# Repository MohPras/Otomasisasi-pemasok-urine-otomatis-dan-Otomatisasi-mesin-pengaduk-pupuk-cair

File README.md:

# Otomasisasi-pemasok-urine-otomatis-dan-Otomatisasi-mesin-pengaduk-pupuk-cair

Alat ini berfungsi untuk membuat pupuk secara otomatis dimana letak otomasisasinya itu pada saat memasukan urine domba dan saat proses pengadukan. Cara kerja alat ini pertama saat pushbutton urine ditekan makan dia akan mengeluarkan urine sebanyak yang kita mau, untuk perhitunganya menggunakan flow sensor sedangkan kran otomatis menggunakan valve sehingga kita bisa dengan mudah mengatur kapasitas urine yang akan dimasukan. Setelah kaspitas air sudah sesuai dengan yang dimau kran akan tertutup otomatis. dan selanjutnya relay akan mengaktifkan motor pengaduknya selama 20 menit dan pupuk pun jadi.

Alat dan bahan
- motor + gir box
- flow sensor
- valve
- sensor proximity untuk mengetahui berapa banyak urine dalam tampungan
- relay sebagai saklar otomatis

Design PCB

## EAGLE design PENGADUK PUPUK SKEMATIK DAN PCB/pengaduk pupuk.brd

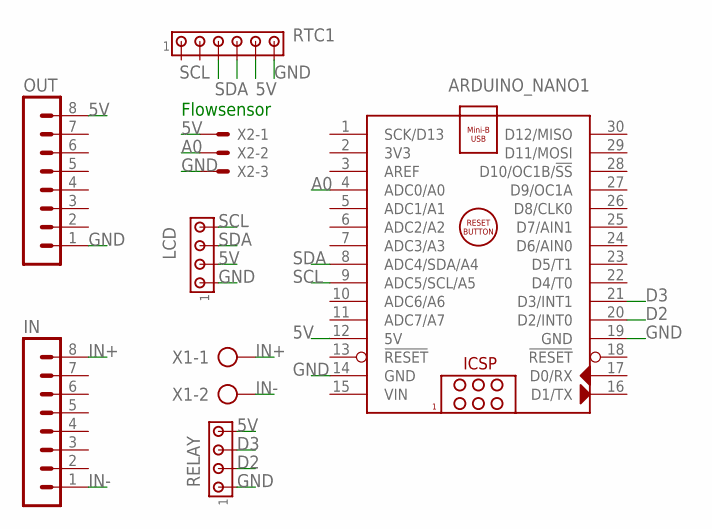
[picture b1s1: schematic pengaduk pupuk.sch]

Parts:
ARDUINO_NANO1: ARDUINO_NANO
IN: MA08-1
LCD: MTA04-100; 10X04MTA
OUT: MA08-1
RELAY: MTA04-100; 10X04MTA
RTC1: MTA06-100; 10X06MTA
X1: AK500/2-H
X2: KK-156-3

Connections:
5V: ARDUINO_NANO1.12 (5V), LCD.2, OUT.8, RELAY.4, RTC1.5, X2.1
A0: ARDUINO_NANO1.4 (ADC0/A0), X2.2
D2: ARDUINO_NANO1.20 (D2/INT0), RELAY.2
D3: ARDUINO_NANO1.21 (D3/INT1), RELAY.3
GND: ARDUINO_NANO1.14 (GND), ARDUINO_NANO1.19 (GND), LCD.1, OUT.1, RELAY.1, RTC1.6, X2.3
IN+: IN.8, X1.1
IN-: IN.1, X1.2
SCL: ARDUINO_NANO1.9 (ADC5/SCL/A5), LCD.4, RTC1.3
SDA: ARDUINO_NANO1.8 (ADC4/SDA/A4), LCD.3, RTC1.4
VIN: ARDUINO_NANO1.15 (VIN)

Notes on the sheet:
Flowsensor

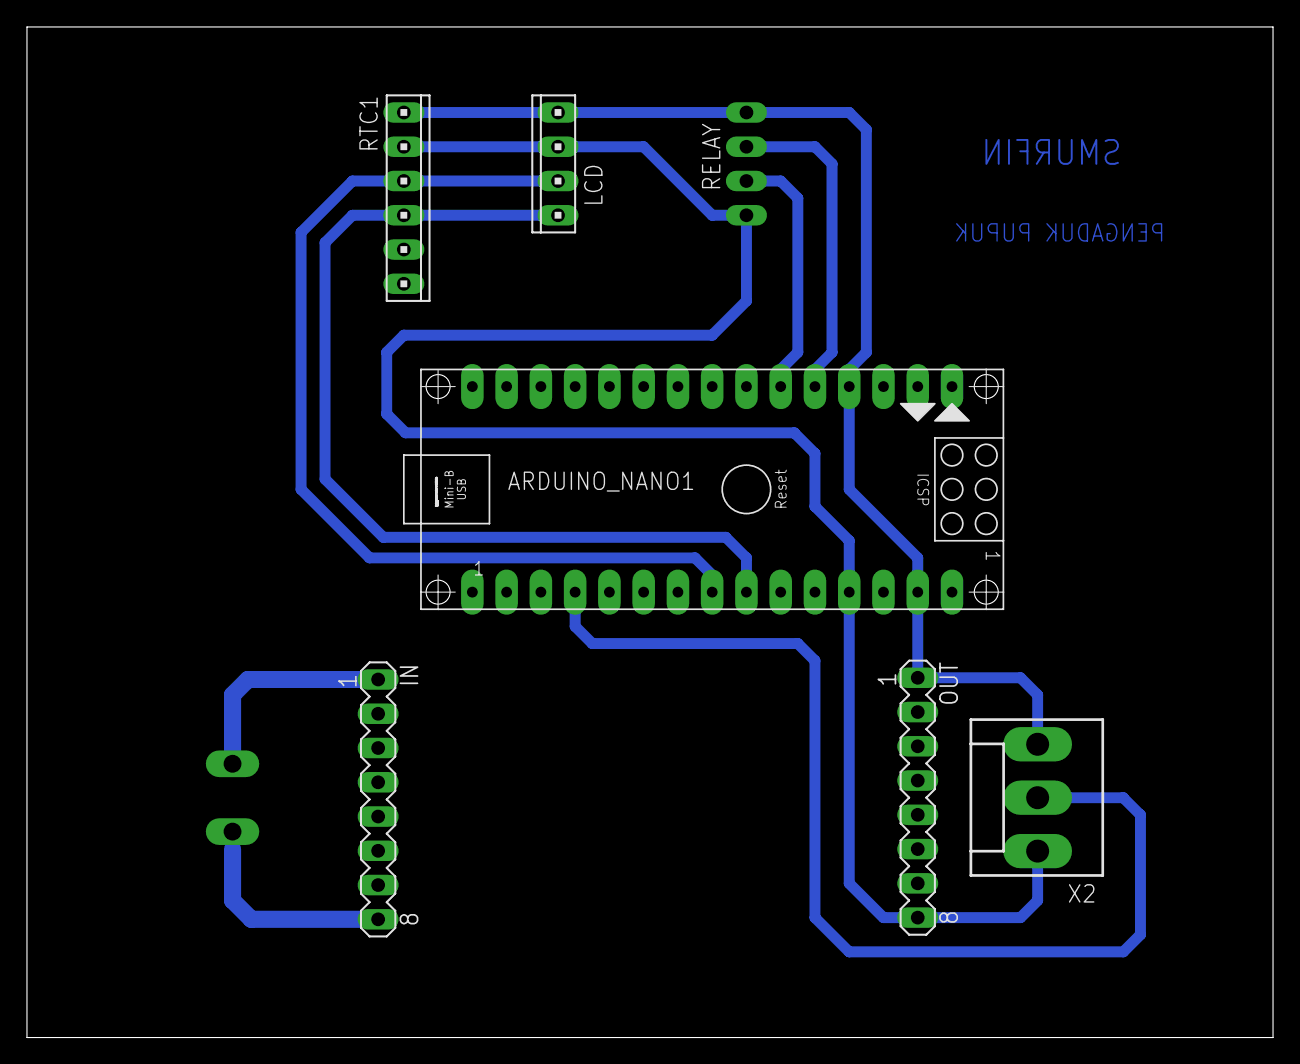
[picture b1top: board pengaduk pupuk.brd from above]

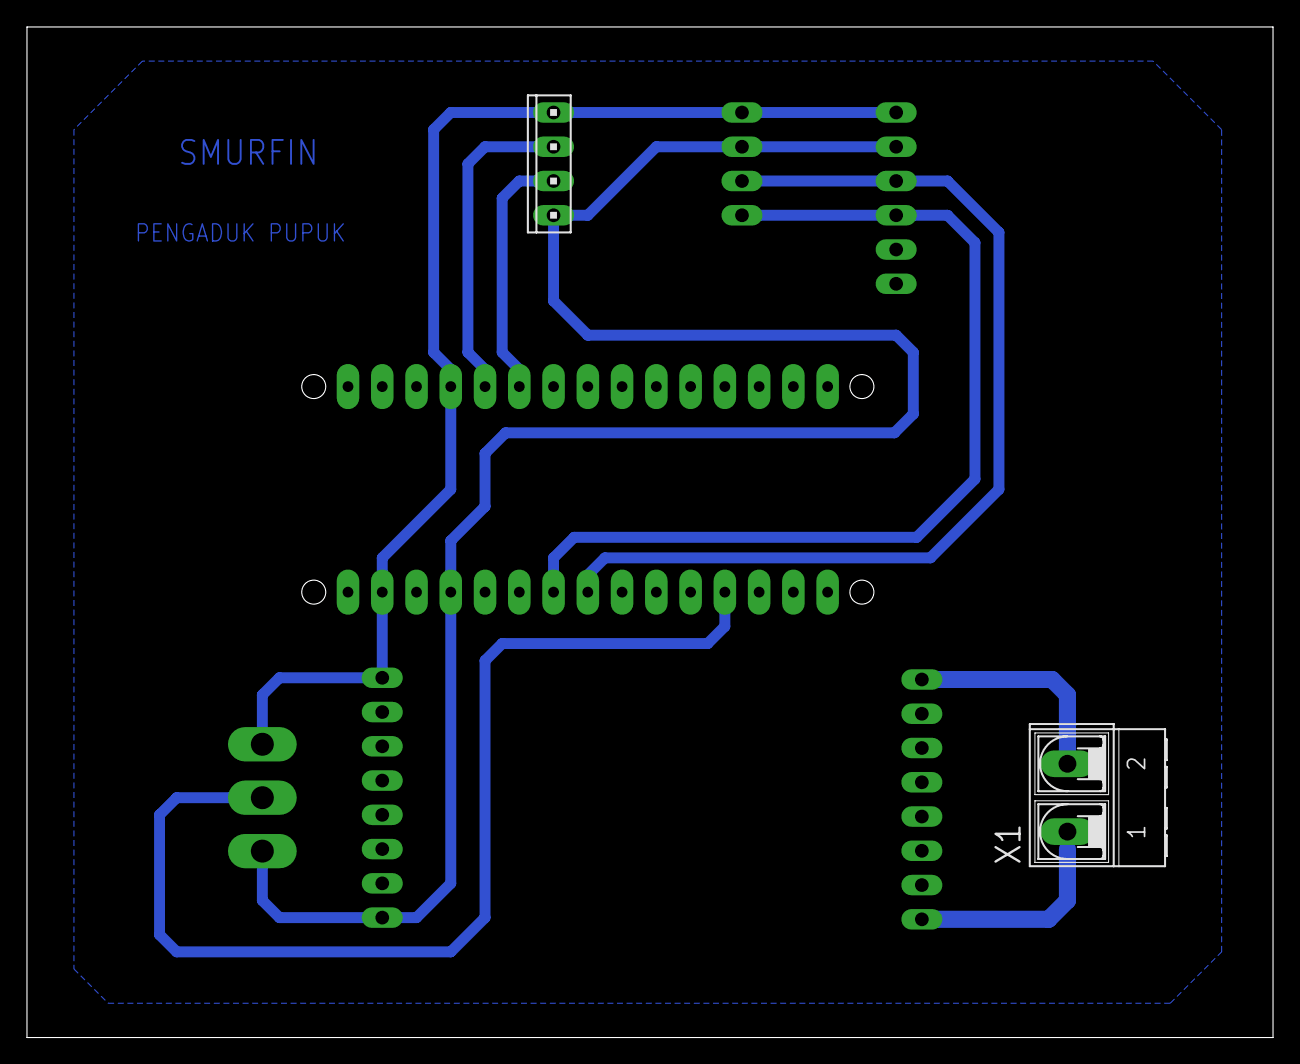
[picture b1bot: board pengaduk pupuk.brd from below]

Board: 2 copper layers, 92.4 x 74.9 mm, 8 parts (2 on the bottom side), 9 nets.
